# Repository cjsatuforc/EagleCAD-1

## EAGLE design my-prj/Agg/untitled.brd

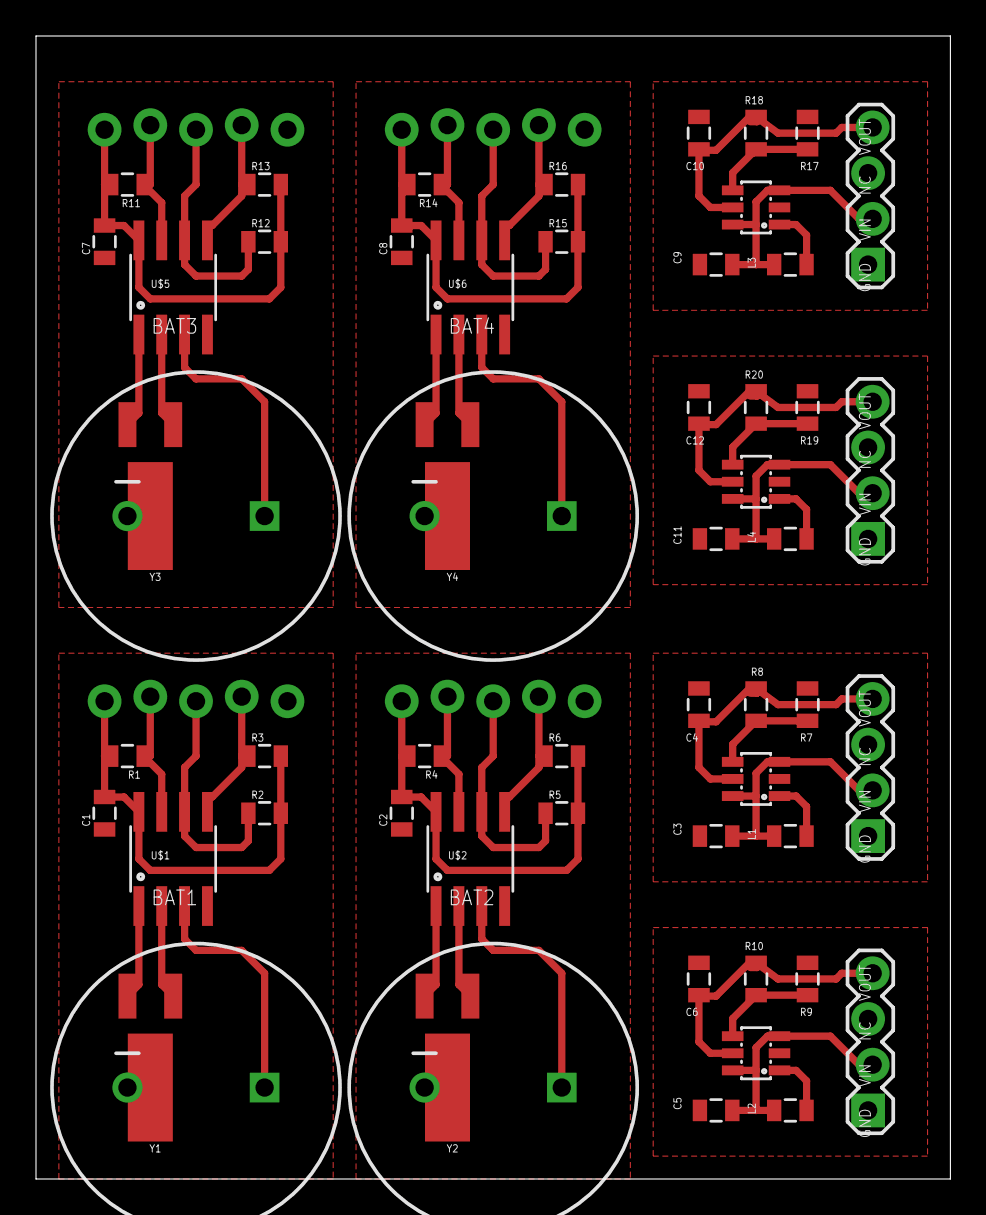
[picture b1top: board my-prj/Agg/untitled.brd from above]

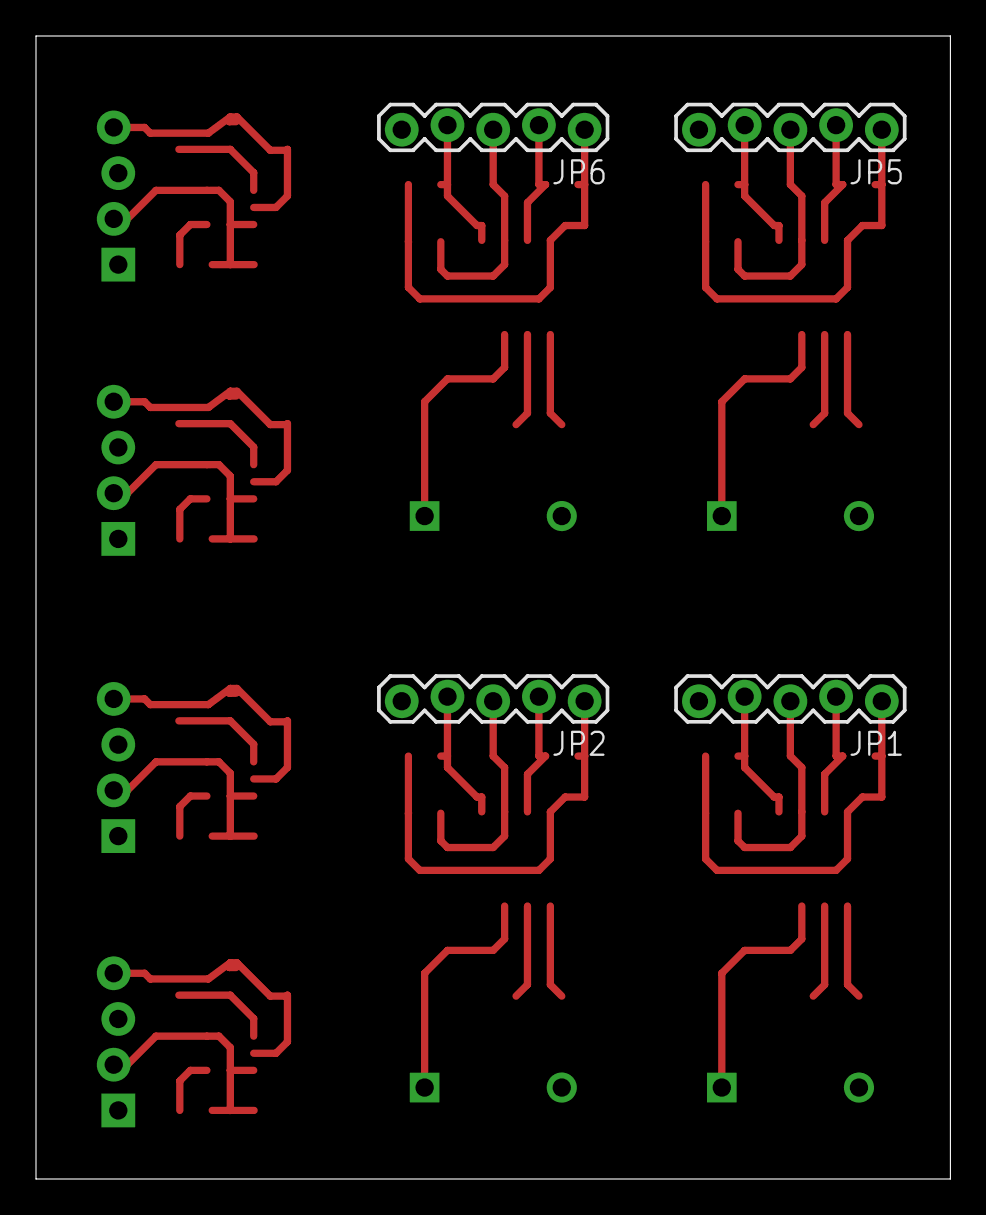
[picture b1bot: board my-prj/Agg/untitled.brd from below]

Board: 2 copper layers, 50.8 x 63.5 mm, 60 parts (4 on the bottom side), 52 nets.

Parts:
BAT1, BAT2, BAT3, BAT4: CPOL-RADIAL-1000UF-63V
C1, C2, C3, C4, C5, C6, C7, C8, C9, C10, C11, C12: 0805
JP1, JP2, JP5, JP6: 1X05_LOCK
JP3, JP4, JP7, JP8: 1X04_LOCK
L1, L2, L3, L4: 0805
R1, R2, R3, R4, R5, R6, R7, R8, R9, R10, R11, R12, R13, R14, R15, R16, R17, R18, R19, R20: 0805
U$1, U$2, U$5, U$6: BQ32000; SO08
U$3, U$4, U$7, U$8: TLV61220; SOT23-6L
Y1, Y2, Y3, Y4: CRYSTAL-32KHZ-SMD

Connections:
GND: BAT1.2, C1.1, JP1.5, U$1.4
GND1: BAT2.2, C2.1, JP2.5, U$2.4
GND2: C3.2, C4.2, JP3.1, R7.1, U$3.2
GND3: C5.2, C6.2, JP4.1, R9.1, U$4.2
GND4: BAT3.2, C7.1, JP5.5, U$5.4
GND5: BAT4.2, C8.1, JP6.5, U$6.4
GND6: C9.2, C10.2, JP7.1, R17.1, U$7.2
GND7: C11.2, C12.2, JP8.1, R19.1, U$8.2
unnamed: BAT1.1, U$1.3
unnamed: JP1.2, R1.1, U$1.7
unnamed: JP1.3, R2.1, U$1.6
unnamed: JP1.4, R3.1, U$1.5
unnamed: U$1.1, Y1.X2
unnamed: U$1.2, Y1.X1
unnamed: JP2.2, R4.1, U$2.7
unnamed: JP2.3, R5.1, U$2.6
unnamed: JP2.4, R6.1, U$2.5
unnamed: U$2.1, Y2.X2
unnamed: U$2.2, Y2.X1
unnamed: BAT2.1, U$2.3
unnamed: L1.2, U$3.1
unnamed: R7.2, R8.1, U$3.4
unnamed: C4.1, JP3.4, R8.2, U$3.5
unnamed: L2.2, U$4.1
unnamed: R9.2, R10.1, U$4.4
unnamed: C6.1, JP4.4, R10.2, U$4.5
unnamed: JP5.2, R11.1, U$5.7
unnamed: JP5.3, R12.1, U$5.6
unnamed: JP5.4, R13.1, U$5.5
unnamed: U$5.1, Y3.X2
unnamed: U$5.2, Y3.X1
unnamed: BAT3.1, U$5.3
unnamed: JP6.2, R14.1, U$6.7
unnamed: JP6.3, R15.1, U$6.6
unnamed: JP6.4, R16.1, U$6.5
unnamed: U$6.1, Y4.X2
unnamed: U$6.2, Y4.X1
unnamed: BAT4.1, U$6.3
unnamed: L3.2, U$7.1
unnamed: R17.2, R18.1, U$7.4
unnamed: C10.1, JP7.4, R18.2, U$7.5
unnamed: L4.2, U$8.1
unnamed: R19.2, R20.1, U$8.4
unnamed: C12.1, JP8.4, R20.2, U$8.5
VCC: C1.2, JP1.1, R1.2, R2.2, R3.2, U$1.8
VCC1: C2.2, JP2.1, R4.2, R5.2, R6.2, U$2.8
VCC2: C7.2, JP5.1, R11.2, R12.2, R13.2, U$5.8
VCC3: C8.2, JP6.1, R14.2, R15.2, R16.2, U$6.8
VIN: C3.1, JP3.2, L1.1, U$3.3, U$3.6
VIN1: C5.1, JP4.2, L2.1, U$4.3, U$4.6
VIN2: C9.1, JP7.2, L3.1, U$7.3, U$7.6
VIN3: C11.1, JP8.2, L4.1, U$8.3, U$8.6

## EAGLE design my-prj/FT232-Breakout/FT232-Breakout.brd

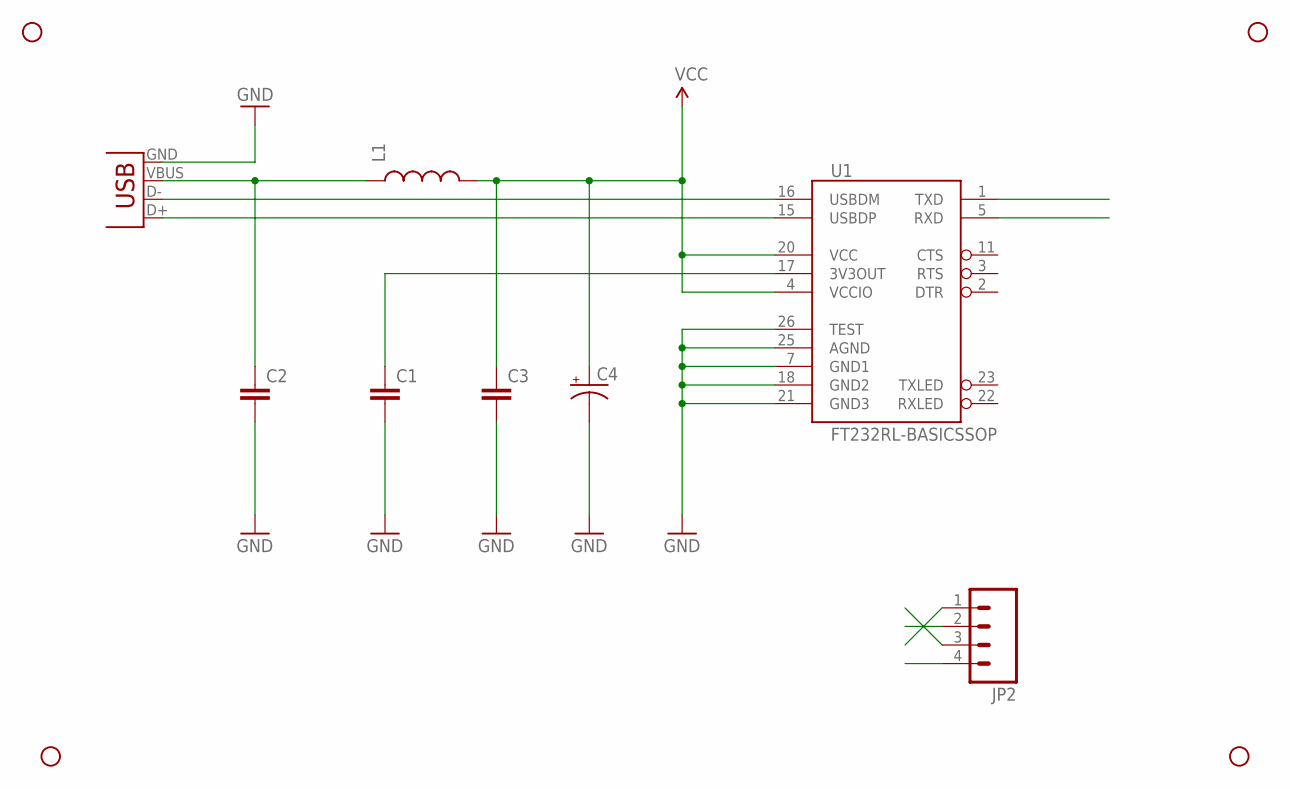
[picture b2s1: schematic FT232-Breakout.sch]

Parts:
C1, C2, C3: CAP0603-CAP; 0603-CAP
C4: CAP_POL1206; EIA3216
JP1: USB-B; USB-B-PTH
JP2: M04PTH; 1X04
L1: INDUCTOR0603; 0603
STANDOFF1, STANDOFF2, STANDOFF3, STANDOFF4: STAND-OFF
U1: FT232RL-BASICSSOP; SSOP28DB

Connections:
GND: C1.2, C2.2, C3.2, C4.C (-), JP1.GND, JP2.1, U1.7 (GND1), U1.18 (GND2), U1.21 (GND3), U1.25 (AGND), U1.26 (TEST)
unnamed: C2.1, JP1.VBUS, L1.1
unnamed: C1.1, U1.17 (3V3OUT)
unnamed: JP1.D-, U1.16 (USBDM)
unnamed: JP1.D+, U1.15 (USBDP)
RX: JP2.2, U1.5 (RXD)
TX: JP2.3, U1.1 (TXD)
VCC: C3.1, C4.A (+), JP2.4, L1.2, U1.4 (VCCIO), U1.20 (VCC)

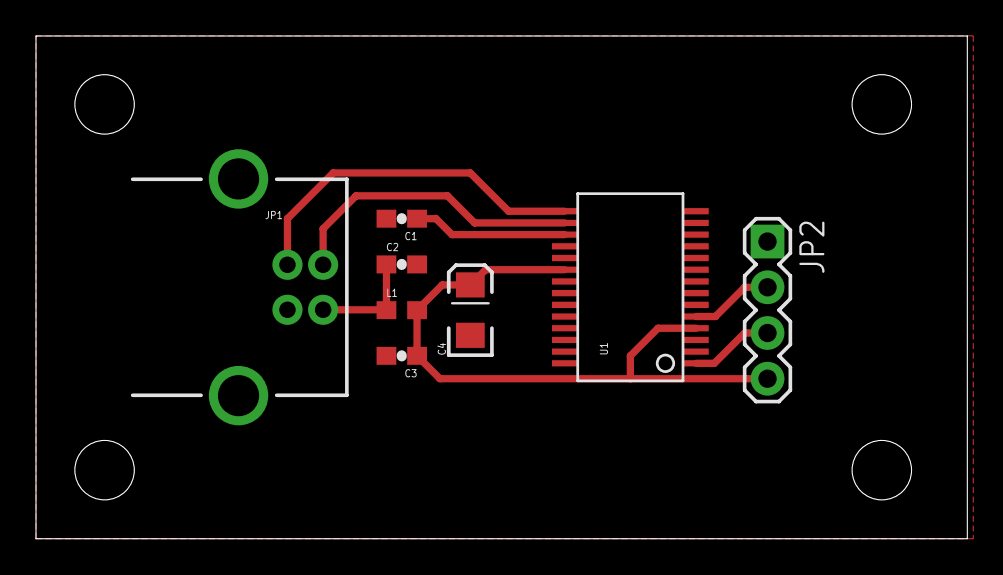
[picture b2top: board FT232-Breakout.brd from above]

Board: 2 copper layers, 51.7 x 27.9 mm, 12 parts (0 on the bottom side), 8 nets.

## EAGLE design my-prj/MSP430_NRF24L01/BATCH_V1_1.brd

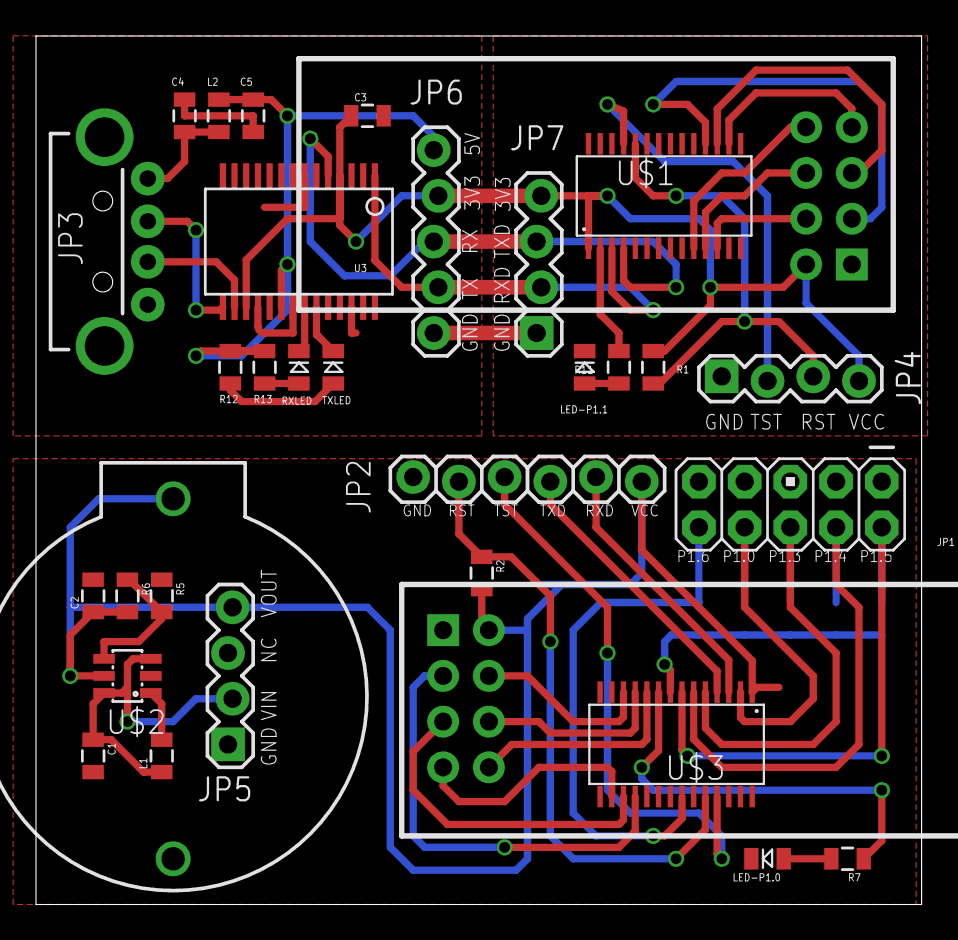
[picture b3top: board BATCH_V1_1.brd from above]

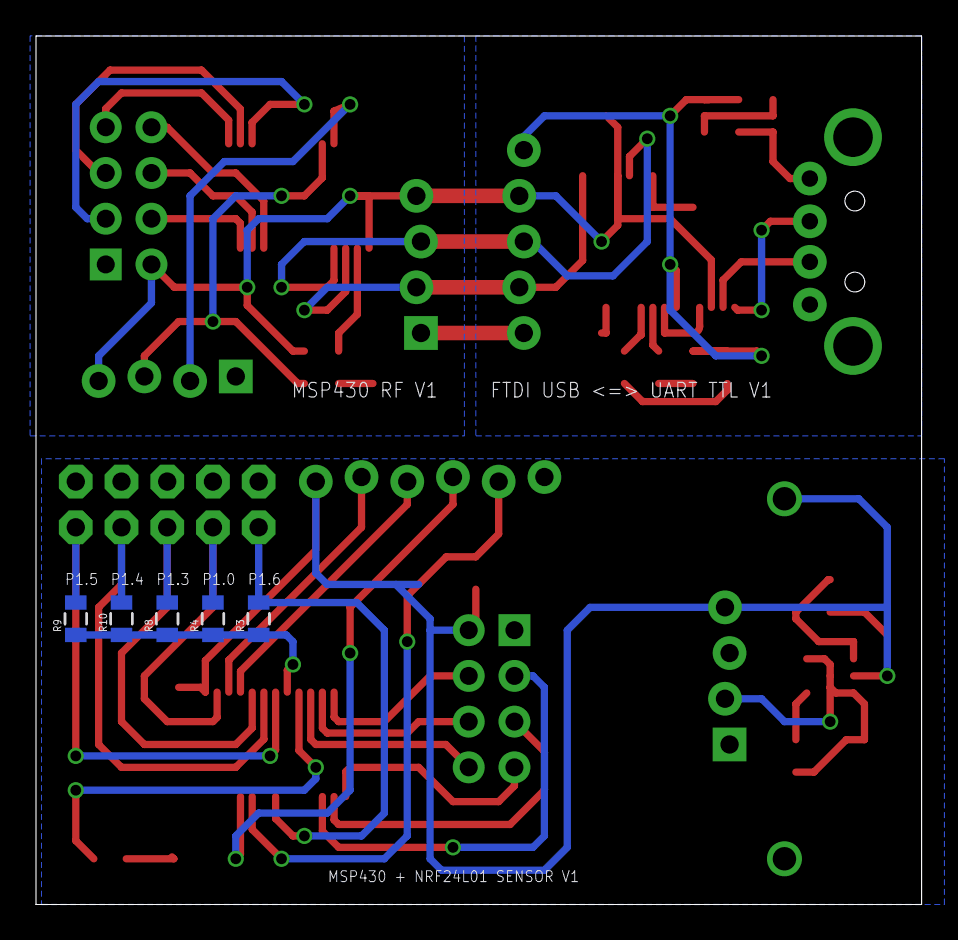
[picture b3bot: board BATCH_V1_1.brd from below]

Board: 4 copper layers, 49.2 x 48.2 mm, 38 parts (5 on the bottom side), 45 nets.

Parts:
BAT1: BATTCOM_20MM_PTH
C1, C2: 0805
C3, C4: 0.1uF; 0805
C5: 10uF; 0805
JP1: M05X2PTH; AVR_ICSP
JP2: 1X06_LOCK
JP3: USB-B; USB-A-H
JP4, JP5, JP7: 1X04_LOCK
JP6: 1X05_LOCK
L1, L2: 0805
LED-P1.0, LED-P1.1: LED-0805
R1, R2, R3, R4, R8, R9, R10: 47K; 0805
R5, R6: 0805
R7, R11: 220; 0805
R12, R13: 330; 0805
RXLED: LED-0805
TXLED: LED-0805
U1, U2: NRF24L01-4X2
U3: FT232RL-BASICSSOP; SSOP28DB
U$1, U$3: G2XX3---PW28; PW28
U$2: TI-TLV61220; SOT23-6L

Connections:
5V: C5.1, JP6.5, L2.2, R12.1, R13.1, U3.20
GND: BAT1.2, C1.2, C2.2, JP1.1, JP1.3, JP1.5, JP1.7, JP1.9, JP2.6, JP5.1, LED-P1.0.C, R5.1, U2.1, U$2.2, U$3.28
GND1: C3.2, C4.2, C5.2, JP3.VBUS, JP4.1, JP6.1, JP7.1, LED-P1.1.C, U1.1, U3.7, U3.18, U3.21, U3.25, U3.26, U$1.28
unnamed: R3.1, R4.1, R8.1, R9.1, R10.1, U$3.8
unnamed: U1.3, U$1.18
unnamed: U1.5, U$1.17
unnamed: U1.7, U$1.16
unnamed: U1.6, U$1.11
unnamed: U1.4, U$1.12
unnamed: R13.2, RXLED.A
unnamed: LED-P1.1.A, R11.2
unnamed: RXLED.C, U3.22
unnamed: R12.2, TXLED.A
unnamed: TXLED.C, U3.23
unnamed: U1.8, U$1.10
unnamed: L1.2, U$2.1
unnamed: R5.2, R6.1, U$2.4
unnamed: LED-P1.0.A, R7.2
unnamed: C4.1, JP3.GND, L2.1
unnamed: U2.3, U$3.18
unnamed: U2.5, U$3.17
unnamed: U2.7, U$3.16
unnamed: U2.6, U$3.11
unnamed: U2.4, U$3.12
unnamed: U2.8, U$3.10
unnamed: R7.1, U$3.9
unnamed: R11.1, U$1.2
P1.0: JP1.8, R4.2, U$3.2
P1.3: JP1.6, R8.2, U$3.5
P1.4: JP1.4, R10.2, U$3.6
P1.5: JP1.2, R9.2, U$3.7
P1.6: JP1.10, R3.2, U$3.22
RESET: JP2.5, R2.1, U$3.24
RESET1: JP4.3, R1.1, U$1.24
RX: JP6.3, JP7.3, U3.5, U$1.4
RXD: JP2.2, U$3.3
TEST: JP2.4, U$3.25
TEST1: JP4.2, U$1.25
TX: JP6.2, JP7.2, U3.1, U$1.3
TXD: JP2.3, U$3.4
USBDM: JP3.D-, U3.16
USBDP: JP3.D+, U3.15
VCC: BAT1.1, C2.1, JP2.1, JP5.4, R2.2, R6.2, U2.2, U$2.5, U$3.1
VCC1: C3.1, JP4.4, JP6.4, JP7.4, R1.2, U1.2, U3.4, U3.17, U$1.1
VIN: C1.1, JP5.2, L1.1, U$2.3, U$2.6

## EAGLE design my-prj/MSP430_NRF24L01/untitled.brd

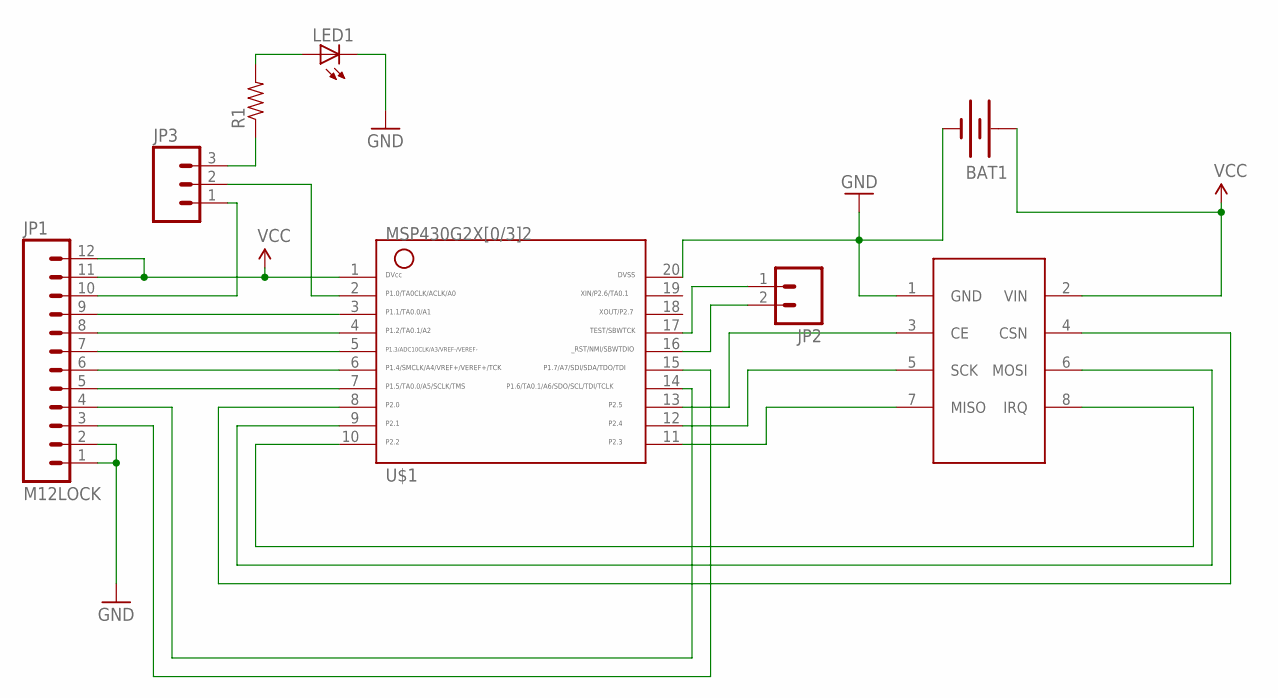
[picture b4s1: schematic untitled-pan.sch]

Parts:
BAT1: BATTERY20PTH; BATTCOM_20MM_PTH
JP1: M12LOCK; 1X12_LOCK
JP2: M02PTH; 1X02
JP3: M03PTH; 1X03
LED1: LED3MM
R1: RESISTORAXIAL-0.3; AXIAL-0.3
U1: NRF24L01-4X2
U$1: G2X[0/3]2---N20; N20

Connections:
GND: BAT1.2 (-), JP1.1, JP1.2, LED1.K (C), U1.1 (GND), U$1.20
unnamed: U1.3 (CE), U$1.13
unnamed: U1.8 (IRQ), U$1.10
unnamed: U1.7 (MISO), U$1.11
unnamed: U1.5 (SCK), U$1.12
unnamed: JP1.4, U$1.14
unnamed: JP1.3, U$1.15
unnamed: JP1.6, U$1.6
unnamed: JP1.7, U$1.5
unnamed: JP1.8, U$1.4
unnamed: JP1.9, U$1.3
unnamed: JP3.2, U$1.2
unnamed: JP1.5, U$1.7
unnamed: JP2.2, U$1.16
unnamed: JP2.1, U$1.17
unnamed: JP3.3, R1.P$1 (1)
unnamed: JP1.10, JP3.1
unnamed: U1.6 (MOSI), U$1.9
unnamed: U1.4 (CSN), U$1.8
unnamed: LED1.A, R1.P$2 (2)
VCC: BAT1.1 (+), JP1.11, JP1.12, U1.2 (VIN), U$1.1

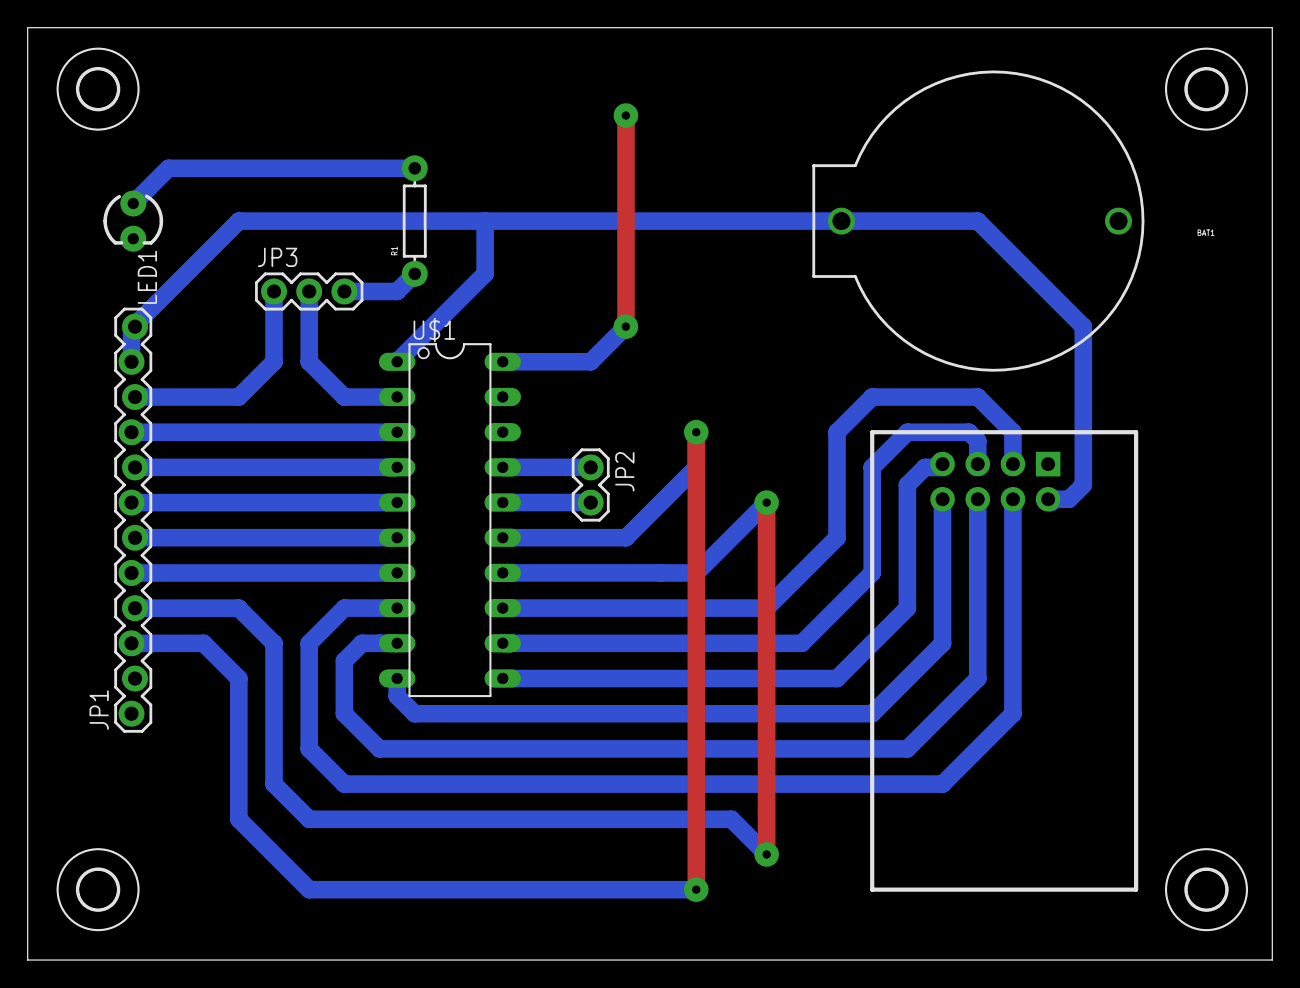
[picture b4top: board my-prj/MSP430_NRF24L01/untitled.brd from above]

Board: 2 copper layers, 89.8 x 67.3 mm, 12 parts (0 on the bottom side), 21 nets.

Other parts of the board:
U$2, U$3, U$4, U$5: 2,8

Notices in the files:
parts and their libraries:
SparkFun-Passives: Licensing: CC v3.0 Share-Alike You are welcome to use this library for commercial purposes.
